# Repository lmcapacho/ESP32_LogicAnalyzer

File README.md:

# ESP32 LogicAnalyzer

A [SUMP](http://dangerousprototypes.com/docs/The_Logic_Sniffer%27s_extended_SUMP_protocol) compatible 16Bit Logic Analyzer for ESP32 MCUs.

## Specifications

- Uses **ESP32 I2S DMA** and can capture speeds up to **20 MHz**.
- Supports **8-bit** and **16-bit** operations.
- Maximum **128k** samples (even in 8-bit capturing mode).
- RLE compression supported.
- Default OLS port is **UART0** with a default baud rate of **912600**.
- You can configure UART ports and high-speed baud rates for OLS communication by editing the definitions in LogicAnalyzerConfig.h.

### Supported Environments

| Environment    | Status | Details                                 |
|----------------|--------|-----------------------------------------|
| PlatformIO     | ✅     | Tested with `platform-espressif32@6.11.0` |
| Arduino IDE    | ✅     | Tested with `Arduino-ESP32 core 3.3.7` |

### Under Development

- WROOVER modules support **2M** samples but only up to **2 MHz** due to bandwidth limits on PSRAM access.
- Analog input support.

## Quick Start Guide

### Environments

#### PlatformIO

1. Install [PlatformIO](https://platformio.org/) in VS Code.
2. Open the project folder in PlatformIO.
3. Build the project and flash it to your ESP32.

#### Arduino IDE

1. Install the **ESP32 board support** via the Boards Manager (`esp32 by Espressif Systems`).
2. Open the sketch in `ESP32_LogicAnalyzer/ESP32_LogicAnalyzer.ino`.
3. Select the board you're using (e.g. `ESP32 Dev Module`).
4. Use ESP32 Arduino core version `3.3.7`.
5. Click **Upload**.

**Important:** If you're using UART0 for OLS communication, set **Core Debug Level = None** in the Arduino IDE before compiling, especially for captures above 10 MHz.

### PulseView

Open PulseView with:
```bash
pulseview -D -d ols:conn=/dev/ttyUSB0::serialcomm=921600/8n1
```
Or from the GUI, connect the device and select **Openbench Logic Sniffer & SUMP compatibles (ols)**.

RLE can be enabled in Device configuration dialog:

For more details, see the [PulseView documentation](https://sigrok.org/wiki/PulseView).

## Connections

| Pin      | Connection                              |
|----------|-----------------------------------------|
| clk_in   | GPIO23 (connect to **clk_out**)         |
| clk_out  | GPIO22 (connect to **clk_in**)          |
| Ground   | Connect the target device's GND to the ESP32 GND         |
| Channels | CH15 - CH0 (connect your signals here)  |

⚠️ **Warning:** GPIO23 is used for I2S input clock and GPIO22 for LEDC output clock.  
Do not use these pins for general I/O. If needed, change them in the code and rewire accordingly.

## Hardware Design (KiCad)

This project includes a custom PCB designed in **KiCad 9** to connect the ESP32 DevKitC V1 with logic analyzer channels and level shifters.

All hardware-related files are located in the [`hardware/`](./hardware) folder and include:

- Complete KiCad project (`.kicad_pro`, `.kicad_sch`, `.kicad_pcb`)
- BOM (`BOM.xlsx`) and CPL (`CPL1.xlsx`) for assembly
- Gerber files (`hardware/gerbers/`) for PCB fabrication
- Optional UART2 debug port
- Level shifter ICs (SN74LVC245A) for 5V input compatibility

> ⚠️ The design is currently under validation. Use at your own risk until physical tests are completed.

### PCB Preview

## Attributions

This project is a fork of [ESP32_LogicAnalyzer](https://github.com/EUA/ESP32_LogicAnalyzer), created by [Erdem U. Altinyurt](https://github.com/EUA).

This project uses code from:
- [esp32-cam-demo](https://github.com/igrr/esp32-cam-demo) for I2S DMA.
- [Arduino Logic Analyzer](https://github.com/gillham/logic_analyzer) as a SUMP protocol "template".

## License

This project is licensed under the **GPL 3.0 License**. See the [LICENSE](LICENSE) file for details.

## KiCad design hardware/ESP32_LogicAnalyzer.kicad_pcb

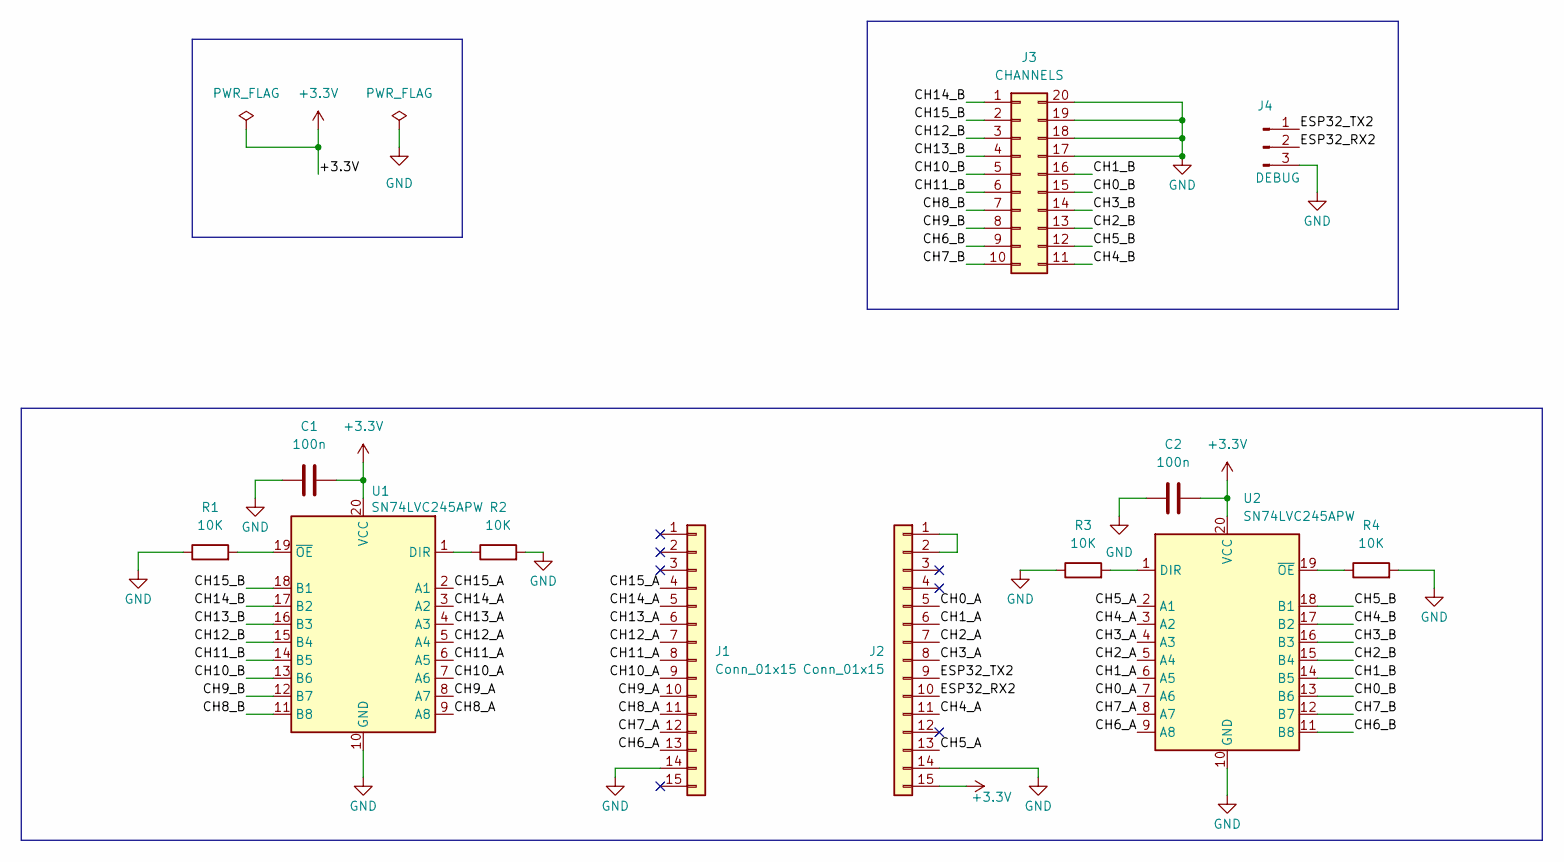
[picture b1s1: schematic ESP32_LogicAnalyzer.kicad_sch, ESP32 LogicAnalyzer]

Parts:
C1, C2: 100n; C_0603_1608Metric
J1, J2: Conn_01x15; PinSocket_1x15_P2.54mm_Vertical
J3: CHANNELS; PinHeader_2x10_P2.54mm_Vertical
J4: DEBUG; PinHeader_1x03_P2.54mm_Vertical
R1, R2, R3, R4: 10K; R_0603_1608Metric
U1, U2: SN74LVC245APW; TSSOP-20_4.4x6.5mm_P0.65mm

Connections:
+3.3V: C1.2, C2.2, J2.15, U1.20 (VCC), U2.20 (VCC)
/CH0_A: J2.5, U2.7 (A6)
/CH0_B: J3.15, U2.13 (B6)
/CH1_A: J2.6, U2.6 (A5)
/CH1_B: J3.16, U2.14 (B5)
/CH2_A: J2.7, U2.5 (A4)
/CH2_B: J3.13, U2.15 (B4)
/CH3_A: J2.8, U2.4 (A3)
/CH3_B: J3.14, U2.16 (B3)
/CH4_A: J2.11, U2.3 (A2)
/CH4_B: J3.11, U2.17 (B2)
/CH5_A: J2.13, U2.2 (A1)
/CH5_B: J3.12, U2.18 (B1)
/CH6_A: J1.13, U2.9 (A8)
/CH6_B: J3.9, U2.11 (B8)
/CH7_A: J1.12, U2.8 (A7)
/CH7_B: J3.10, U2.12 (B7)
/CH8_A: J1.11, U1.9 (A8)
/CH8_B: J3.7, U1.11 (B8)
/CH9_A: J1.10, U1.8 (A7)
/CH9_B: J3.8, U1.12 (B7)
/CH10_A: J1.9, U1.7 (A6)
/CH10_B: J3.5, U1.13 (B6)
/CH11_A: J1.8, U1.6 (A5)
/CH11_B: J3.6, U1.14 (B5)
/CH12_A: J1.7, U1.5 (A4)
/CH12_B: J3.3, U1.15 (B4)
/CH13_A: J1.6, U1.4 (A3)
/CH13_B: J3.4, U1.16 (B3)
/CH14_A: J1.5, U1.3 (A2)
/CH14_B: J3.1, U1.17 (B2)
/CH15_A: J1.4, U1.2 (A1)
/CH15_B: J3.2, U1.18 (B1)
/ESP32_RX2: J2.10, J4.2
/ESP32_TX2: J2.9, J4.1
GND: C1.1, C2.1, J1.14, J2.14, J3.17, J3.18, J3.19, J3.20, J4.3, R1.1, R2.2, R3.1, R4.2, U1.10 (GND), U2.10 (GND)
unnamed: J2.1, J2.2
unnamed: R2.1, U1.1 (DIR)
unnamed: R1.2, U1.19 (~OE)
unnamed: R3.2, U2.1 (DIR)
unnamed: R4.1, U2.19 (~OE)

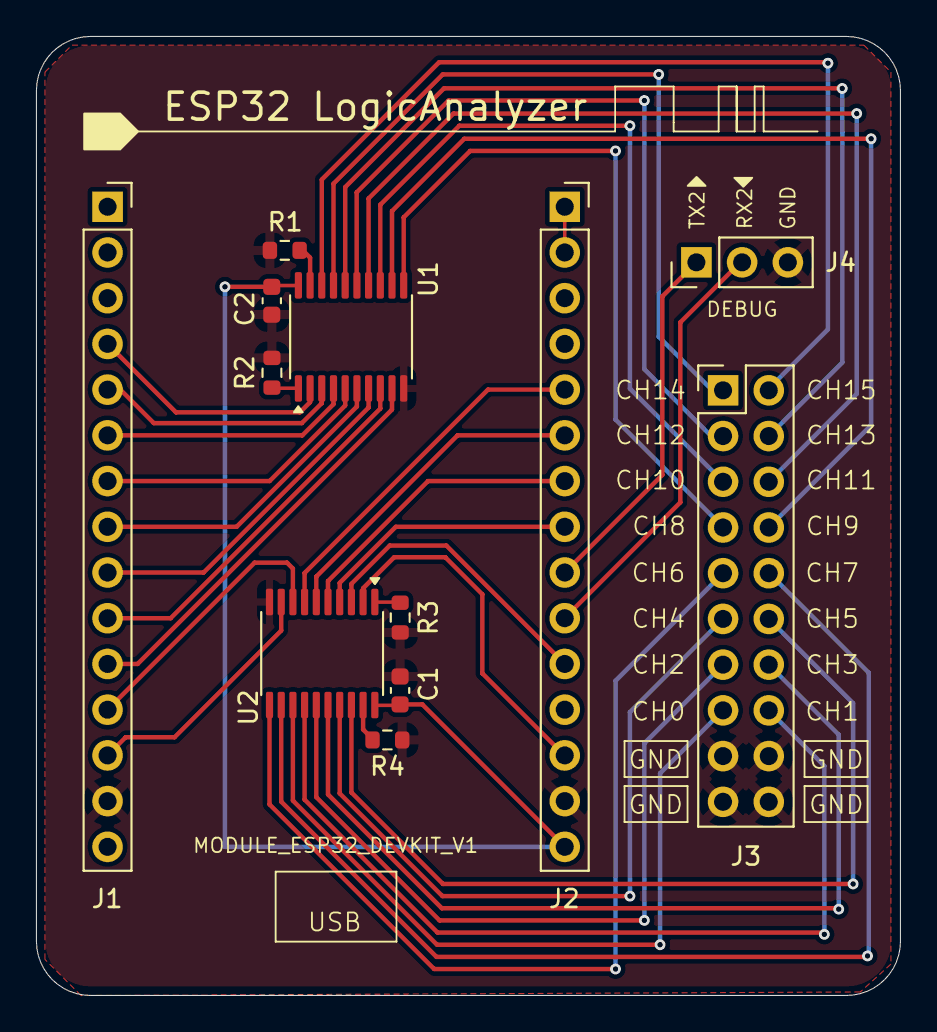
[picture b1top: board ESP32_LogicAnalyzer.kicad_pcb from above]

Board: 2 copper layers, 48.0 x 53.3 mm, 12 parts (0 on the bottom side), 41 nets.

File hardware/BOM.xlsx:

Comment | Designator | Footprint | JLCPCB Part #（optional）
100n | C1,C2 | C_0603_1608Metric | C14663
10K | R1,R2,R3,R4 | R_0603_1608Metric | C101254
CHANNELS | J3 | PinHeader_2x10_P2.54mm_Vertical | C5116480
Conn_01x15 | J1,J2 | PinSocket_1x15_P2.54mm_Vertical | C7499333
DEBUG | J4 | PinHeader_1x03_P2.54mm_Vertical | C2937625
SN74LVC245APW | U1,U2 | TSSOP-20_4.4x6.5mm_P0.65mm | C7848

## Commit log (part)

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2025-02-12 Move code to src folder
2025-02-14 fix: change channel 10 from GPIO20 to GPIO25 to avoid bootloop
2025-02-15 chore: update ESP-IDF version to 5.3
2025-02-22 refactor: change LED pin port to onboard LED
2025-02-23 refactor: order pin channels for better organization
2025-02-23 docs: update copyright notice
2025-02-23 docs: move image to docs/images folder
2025-02-23 docs: upload documentation images
2025-02-23 docs: update README.md
2025-04-16 refactor: extract setup and loop logic into begin and handleCommand functions
2025-04-16 chore: include Arduino.h in header and remove redundant includes
2025-04-16 refactor: move function prototypes from .ino to header file
2025-04-16 fix: add required includes for I2S0 and peripheral control
2025-04-16 refactor: remove global variables cmdByte and cmdBytes
2025-04-16 refactor: remove global dependency on cfg struct
2025-04-16 refactor: add i2s_parallel_buffer_desc_t* buffer as parameter to begin function
2025-04-16 style: rename ledPin to LED_PIN to follow constant naming convention
2025-04-16 feat: add LogicAnalyzerConfig.h with user-editable settings
2025-04-16 docs: update instructions to reference LogicAnalyzerConfig.h
2025-04-18 chore: remove unused variables a, b, c, d
2025-04-18 refactor: rename camera_state_t to logic_analyzer_state_t
2025-04-18 refactor: reorder ESP32_LogicAnalyzer.h
2025-04-18 refactor: rename ESP32_LogicAnalyzer to LogicAnalyzer and create class structure
2025-04-18 refactor: rename ESP32_LogicAnalyzer_I2S_DMA.ino to LogicAnalyzer_I2S_DMA.cpp and move functions into class
2025-04-18 refactor: create LogicAnalyzer_RLE.cpp and move RLE-related methods into it
2025-04-18 refactor: create LogicAnalyzer.cpp and move main logic methods into it
2025-04-18 chore: clean up main .ino file after class refactor
2025-04-19 chore: update platformio.ini to use platform version 6.10.0
2025-04-19 fix: add missing headers for Arduino IDE
2025-04-19 fix: add version check for ESP_ARDUINO_VERSION_MAJOR to support 2.x and 3.x
2025-04-19 chore: reorganize repo structure for Arduino IDE and PlatformIO compatibility
2025-04-19 refactor: remove parameter from begin and make it a member of the class
2025-04-19 refactor: replace global TAG variable with define
2025-04-19 docs: reorganize README structure for clarity
2025-07-14 docs: update channel diagram to reflect new CH0–CH5 mapping
2025-07-14 refactor: reorder CH0–CH5 pins to match updated mapping
2025-08-07 chore: add initial PCB hardware design files using KiCad
2025-08-08 docs: add hardware section to README for KiCad PCB design
2026-02-23 chore: improve gitignore for PlatformIO, VSCode and KiCad
2026-02-23 docs: update supported environment versions
2026-02-25 build: add esp32s3 env and hal scaffolding
2026-02-25 refactor: wire target-selected i2s hal stubs
2026-02-25 refactor: isolate esp32 dma/i2s backend with non-esp32 stubs
2026-02-27 build: restore dual-target compile for esp32dev and esp32s3
2026-02-27 feat: enable baseline esp32s3 hal lifecycle wiring
2026-02-27 refactor: route dma setup/capture calls through hal interface
2026-02-27 build: add include fallbacks for esp32 dma backend headers
2026-02-27 refactor: move esp32s3 dma legacy ops wiring into hal
2026-02-27 chore: add esp32s3 dma hal state validation and diagnostics
2026-03-28 feat: add minimal lcd_cam setup for esp32s3 backend
2026-03-28 feat: wire esp32s3 lcd_cam gdma capture baseline
2026-03-28 chore: add esp32s3 eof capture diagnostics
2026-03-28 refactor: add board-specific pin profile selection
2026-03-28 refactor: restructure esp32s3 dma backend state and helpers
2026-03-29 refactor: clean up temporary esp32s3 smoke test work
2026-04-01 Refactor capture initialization behind common backend layer
2026-04-01 Split capture backend API and isolate ESP32-S3 backend
2026-04-01 Decouple ESP32-S3 native capture flow from legacy logic state
2026-04-02 Bring up native ESP32-S3 CH0 capture in PulseView flow
2026-04-02 Move ESP32-specific capture code under hal and clean sketch entrypoint
2026-04-02 Rename common capture bridge away from i2s_dma
2026-04-05 Rename common capture types away from i2s terminology

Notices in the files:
README.md:
License: GPL 3.0
